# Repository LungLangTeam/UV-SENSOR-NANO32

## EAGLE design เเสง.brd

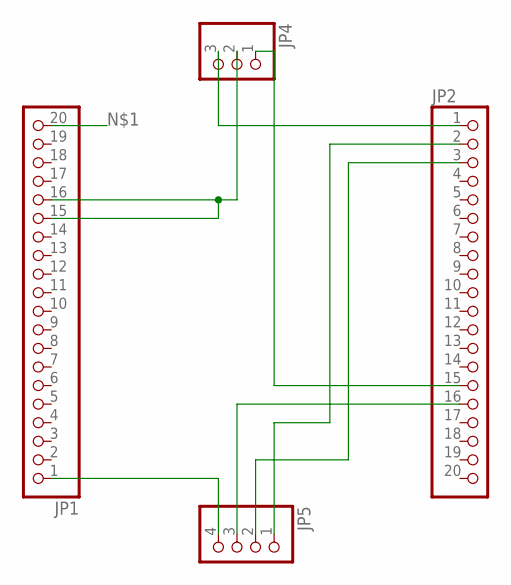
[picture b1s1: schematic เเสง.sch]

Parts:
JP1, JP2: PINHD-1X20; 1X20
JP4: PINHD-1X3; 1X03
JP5: PINHD-1X4; 1X04

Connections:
unnamed: JP1.15, JP1.16, JP4.2
unnamed: JP2.1, JP4.3
unnamed: JP2.15, JP4.1
unnamed: JP1.1, JP5.4
unnamed: JP2.3, JP5.2
unnamed: JP2.2, JP5.1
unnamed: JP2.16, JP5.3

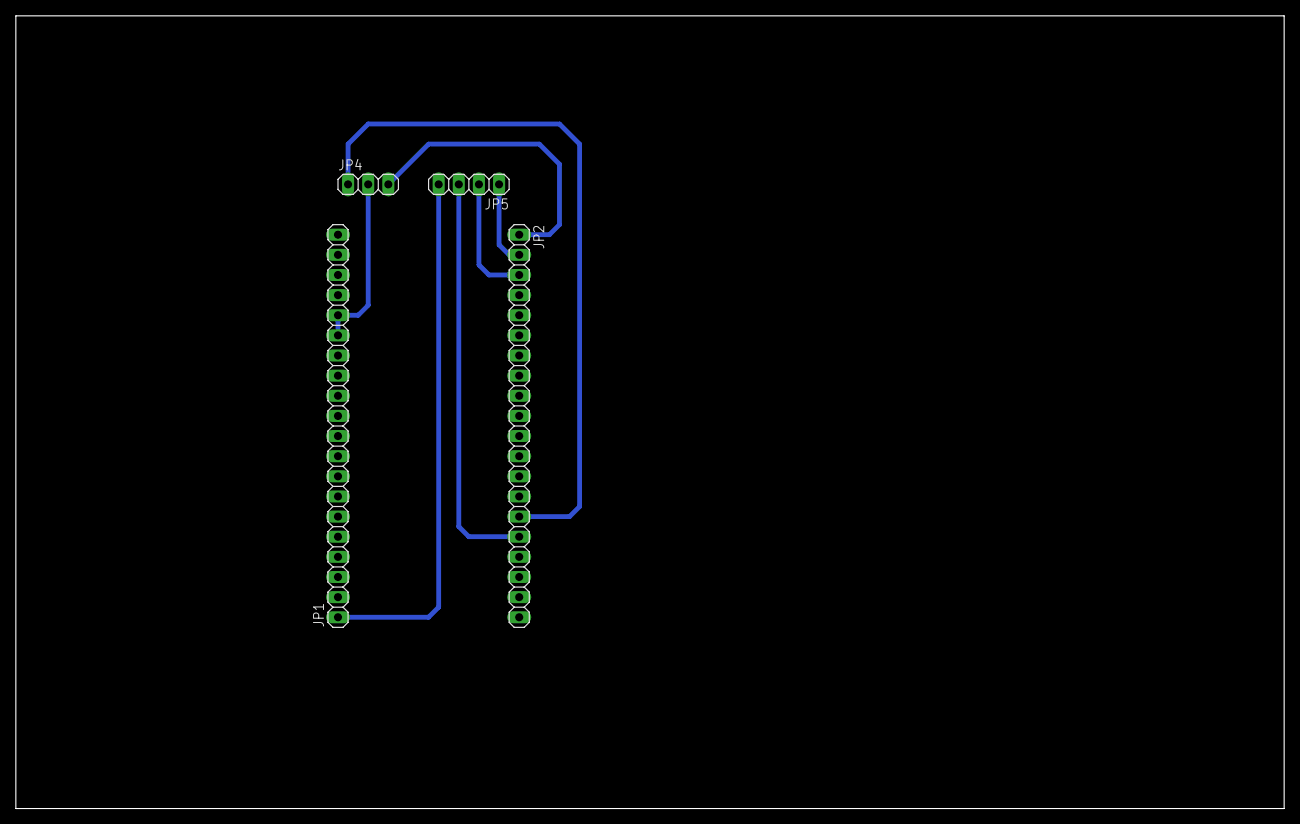
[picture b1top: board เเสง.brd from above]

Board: 2 copper layers, 160.0 x 100.0 mm, 4 parts (0 on the bottom side), 7 nets.
